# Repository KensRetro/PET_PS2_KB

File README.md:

# PET_PS2_KB
An adaptor to connect a PS2 keyboard to a to PET computer.  Plugs directly into the motherboard at the keyboard connector.  
Needs a 5V supply from a convenient place on the motherboard.  There is a ground pin on the KB connector so optionally connect
a ground to the power connector.  The modular jack on the board is optional - Used for programming and debugging the PIC 
program.

Uses a PIC16F18877 to do pretty much everything.

Operation:
MOST keys are translated to the PETS keyboard matrix, see * notes below.
Currently, only the GRAPHIC keyboard is supported, but it would only take a bit of editing to change the tables for a BUSINESS keyboard.

Special keys are as follows:

-- PS2 Key -> PET Key --
* ESC      -> RUN/STOP
* Tilde    -> Left Arrow
* TAB      -> RVS
* SCRLOK   -> (Reboots keyboard interface)***
* END      -> Clear Screen (shift-home)
* Shift 6  -> Up Arrow
* ALT      -> Shift to Graphic on double function keys (1-9 etc.)**
* L/R CTRL -> Hardware equivalnt of SHIFT keys*

Non PET keys are generally No Function

*The PS2 shift keys are  generally treated as a "Soft-Shift" and sent to the PET as needed when a second key is pressed.
If you need to press the SHIFT key alone on the PET use the CTRL key instead.
Limitations of the PS2 keyboard seem to block both SHIFT or CTRL being detected as pressed at the same time, so translating
this to the PET is not possible.  Other multi-key combinations may also not work, but generally it's pretty good.

**Example: to get the graphic on the ! key you need to press SHIFT-ALT-1  (SHIFT-1 for ! and ALT for graphic)

***Once in a while (usually while pressing many keys at once) a key press or release is not detected, pressing the SCROLL-LOCK 
key reboots the PIC and resets the keymap to no keys pressed, usually there's no effect to the PET

How It Works:
 
An interrupt-on-change routine (The PET sets a ROW to read) sets outputs (Columns) for the PET to read back as keypresses.  
A main loop is created to catch bytes from the PS2 keyboard,
Once a PS2 byte is received, it is buffered until bytes stop coming in (A PS2 keypress generates between 2 and 6 bytes)
Once timer2 runs out (which is reset every byte receive, and whose period is slightly longer that the byte to byte interval)
It is assumed the PS2 keyboard has completed sending a Key status change.  The buffer is examined and the appropriate bits are set 
in the memory map setup to represent the PET's keyboard matrix.

Note: routines are optimized for speed, not space, this is to ensure the response is fast enough to suit the PET's 
normal keyboard scan speed

Currently supports GRAPHICS keyboard ONLY - tables would need updating for business style KB

DISCLAIMER: All information is provided 'AS-IS" for informational purposes only.
I have tried to be as accurate as possible but that doesn't mean there are no mistakes. 
Any errors or omissions etc. are your own responsibility.  
There is no Warranty or guarantee of any kind. See licence for details.

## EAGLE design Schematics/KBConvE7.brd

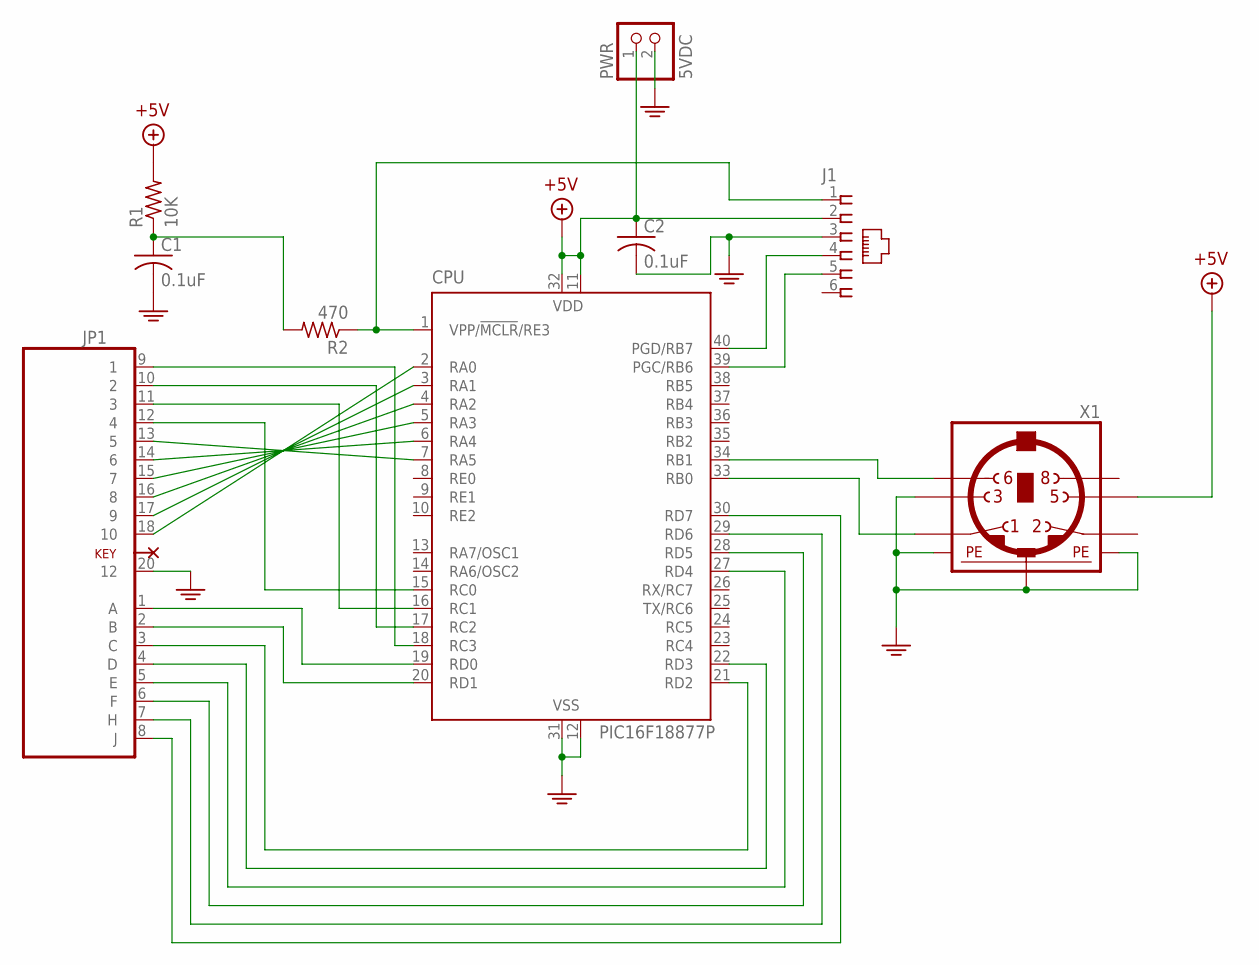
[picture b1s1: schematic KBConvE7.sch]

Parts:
C1, C2: 0.1uF; C025-025X050
CPU: PIC16F18877P; DIL40
J1: 520250-3
JP1: PET_KEYBOARD
PWR: 5VDC; 1X02
R1: 10K; 0207/10
R2: 470; 0207/10
X1: MINI_DIN_6; M_DIN6

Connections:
+5V: C2.1, CPU.11 (VDD), CPU.32 (VDD), J1.2, PWR.1, R1.2, X1.5
GND: C1.2, C2.2, CPU.12 (VSS), CPU.31 (VSS), J1.3, JP1.20 (12), PWR.2, X1.3, X1.SH1 (PE1), X1.SH2 (PE2), X1.SH3 (PE3)
unnamed: CPU.2 (RA0), JP1.18 (10)
unnamed: CPU.3 (RA1), JP1.17 (9)
unnamed: CPU.4 (RA2), JP1.16 (8)
unnamed: CPU.5 (RA3), JP1.15 (7)
unnamed: CPU.6 (RA4), JP1.14 (6)
unnamed: CPU.7 (RA5), JP1.13 (5)
unnamed: CPU.15 (RC0), JP1.12 (4)
unnamed: CPU.16 (RC1), JP1.11 (3)
unnamed: CPU.17 (RC2), JP1.10 (2)
unnamed: CPU.18 (RC3), JP1.9 (1)
unnamed: CPU.19 (RD0), JP1.1 (A)
unnamed: CPU.20 (RD1), JP1.2 (B)
unnamed: CPU.21 (RD2), JP1.3 (C)
unnamed: CPU.22 (RD3), JP1.4 (D)
unnamed: CPU.27 (RD4), JP1.5 (E)
unnamed: CPU.33 (RB0), X1.1
unnamed: CPU.28 (RD5), JP1.6 (F)
unnamed: CPU.29 (RD6), JP1.7 (H)
unnamed: CPU.30 (RD7), JP1.8 (J)
unnamed: C1.1, R1.1, R2.2
unnamed: CPU.39 (PGC/RB6), J1.5
unnamed: CPU.40 (PGD/RB7), J1.4
unnamed: CPU.34 (RB1), X1.6
unnamed: CPU.1 (VPP/!MCLR!/RE3), J1.1, R2.1

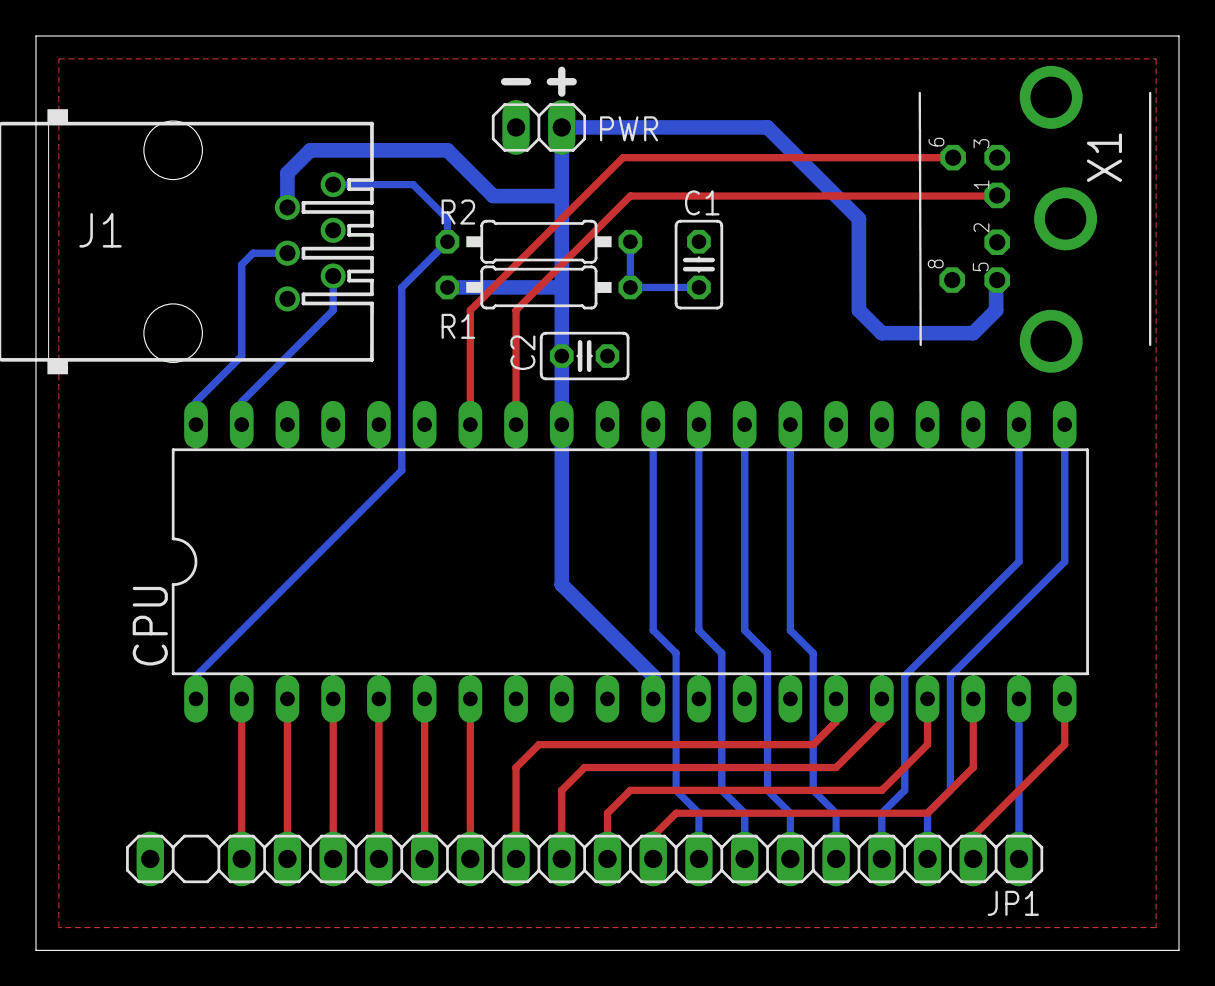
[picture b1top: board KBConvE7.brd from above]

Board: 2 copper layers, 63.5 x 50.8 mm, 9 parts (0 on the bottom side), 26 nets.

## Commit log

2025-02-20 Create folder
